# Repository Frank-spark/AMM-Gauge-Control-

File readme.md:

---
## **Project: ESP32 Gauge Control with H2 Integration**

### **Overview**
This project controls an **analog gauge** and **H2 power supply** using an **ESP32-WROOM-32D**. The gauge reflects the **fill level of a tank** based on readings from a **resistance-based float sensor (240Ω - 30Ω)**. The system implements a **soft-start feature** for H2 power supplies to prevent inrush current, and includes a **web configuration interface** for easy parameter adjustment.

### **Features**
✔ Reads **float sensor resistance** and converts it to gauge display using **PWM control**  
✔ **Smooths the gauge movement** to prevent needle shaking  
✔ **Blinks a backlight** when the fill level is low  
✔ **Soft-start control** (0-5V ramping) for H2 power supplies  
✔ **H2 signal detection** from existing H2 board  
✔ Uses **noise-filtered ADC readings** for reliable measurements  
✔ **Web-based configuration interface** for parameter adjustment  
✔ **WiFi connectivity** with fallback AP mode for setup  
✔ **Watchdog signal generation** (10ms interval)  
✔ **12V to 3.3V Buck Converter** power for ESP32  
✔ **12V to 5V Buck Converter** power for 5V components  

---

## **1. Hardware Setup**
### ** Components Needed**
- **ESP32-WROOM-32D**
- **Float Sensor (240Ω - 30Ω)**
- **10kΩ Pull-up Resistor** (for voltage divider)
- **Gauge (0-100% Analog Display)**
- **IRLB8721 MOSFET** (for PWM gauge control)
- **Level Shifter** (for 12V H2 signal input)
- **0-5V DAC/PWM Filter** (for power supply control)
- **330Ω Resistor + LED** (for backlight warning)
- **4-pin I2C Connector** (for future expansion)
- **2x 4.7kΩ Pull-up Resistors** (for I2C)
- **Watchdog Circuit** (connected to Pin 33)

### ** Wiring Guide**
#### **1️ Power Supply**
| Component | Connection |
|-----------|------------|
| ESP32 VIN | **12V from H2 board gauge light** |
| ESP32 GND | **Common Ground** |
 12V to 5V Buck Converters:

#### **2️ Float Sensor (Resistance Measurement)**
| Pin | Connection |
|-----|------------|
| **ESP32 GPIO 34** | **Voltage divider output** |
| **3.3V** | **10kΩ pull-up resistor** → Float Sensor |
| **GND** | **Float Sensor Ground** |

#### **3️ Gauge Control (PWM Output)**
| Pin | Connection |
|-----|------------|
| **ESP32 GPIO 25** | **MOSFET Gate (IRLB8721)** |
| **Gauge (-)** | **MOSFET Drain** |
| **GND** | **MOSFET Source** |

#### **4️ Power Supply Control**
| Pin | Connection |
|-----|------------|
| **ESP32 GPIO 27** | **PWM Filter** → Power Supply Control |
| **Power Supply CC** | **0-5V Control Input** |

#### **5️ H2 Signal Input**
| Pin | Connection |
|-----|------------|
| **ESP32 GPIO 35** | **Level Shifter Output 10k and 39k VD** |
| **Level Shifter Input** | **H2 Board Coil Signal (12V)** |

#### **6️ Backlight Warning**
| Pin | Connection |
|-----|------------|
| **ESP32 GPIO 26** | **LED via 330Ω Resistor** |
| **GND** | **LED Cathode (-)** |

#### **7️ I2C Expansion Port**
| Pin | Connection |
|-----|------------|
| **1** | **3.3V** |
| **2** | **GPIO 21 (SDA) with 4.7kΩ pull-up** |
| **3** | **GPIO 22 (SCL) with 4.7kΩ pull-up** |
| **4** | **GND** |

#### **8️ Watchdog Signal Output**
| Pin | Connection |
|-----|------------|
| **ESP32 GPIO 33** | **Watchdog Circuit Input** |

---

## **Power Supply Selection**

This project requires efficient **DC-DC buck converters** to step down **12V** to the required operating voltages (**5V** and **3.3V**). Below are the recommended surface-mount buck converters:

### **12V to 5V Buck Converters**
1. **Texas Instruments LM2675**  
   - Step-down voltage regulator with **1A** output.  
   - High efficiency, low component count.  
   - Ideal for powering microcontrollers and peripherals.  
   - [Datasheet](https://www.ti.com/lit/ds/symlink/lm2675.pdf)  

2. **Murata Power Solutions OKI-78SR-5/1.5-W36H-C**  
   - Drop-in replacement for traditional **78xx linear regulators**.  
   - Delivers **5V at up to 1.5A** with minimal heat dissipation.  
   - [Datasheet](https://power.murata.com/pub/data/power/oki-78sr.pdf)  

### **12V to 3.3V Buck Converters**
1. **Texas Instruments TPS54331**  
   - Integrated **3A** step-down regulator with **28V input capability**.  
   - Optimized for high efficiency in embedded systems.  
   - [Datasheet](https://www.ti.com/lit/ds/symlink/tps54331.pdf)  

2. **Analog Devices LTC3621**  
   - **1A synchronous buck converter** with **17V input capability**.  
   - Compact and energy-efficient for low-power applications.  
   - [Datasheet](https://www.analog.com/media/en/technical-documentation/data-sheets/LTC3621.pdf)  

### **Selection Considerations**
- **Current Requirements**: Choose a regulator based on the total current draw of your circuits.  
- **Efficiency**: Higher efficiency reduces heat and improves system stability.  
- **Footprint**: Ensure the selected components fit within the PCB layout.  
- **Availability**: Check supplier stock (e.g., [Digi-Key](https://www.digikey.com/) or [Mouser](https://www.mouser.com/)) before finalizing.  

## **2. Code Explanation**
### **⚙ Main Functionalities**
#### **1️ Setup Function**
- Initializes **PWM control for gauge and power supply**
- Sets up **GPIOs for backlight and H2 signal input**
- Starts **watchdog signal generation**
- Initializes **WiFi and web configuration server**

#### **2️ `loop()` Function**
- Monitors **H2 signal** for power control
- Reads **float sensor resistance**
- Controls **gauge display**
- Manages **power supply ramping**
- Handles **low-level warnings**
- Updates **watchdog signal**
- Processes **DNS requests** (in AP mode)

#### **3️ Power Supply Control**
```cpp
void startPEM() {
    // Ramps power supply control from 0V to max value
    for (current_ramp_value = 0; current_ramp_value <= pemMaxValue; current_ramp_value += pemStepSize) {
        ledc_set_duty(LEDC_LOW_SPEED_MODE, PS_PWM_CHANNEL, current_ramp_value);
        ledc_update_duty(LEDC_LOW_SPEED_MODE, PS_PWM_CHANNEL);
        delay(stepDelayMs);
    }
}
```

#### **4️ Read Float Sensor Resistance**
```cpp
float readFloatSensorResistance(int pin) {
    int adcValue = readSmoothADC(pin);
    float voltage = (adcValue / 4095.0) * 3.3;  

    if (voltage <= 0.1) return MAX_RESISTANCE;  

    float resistance = (voltage / (3.3 - voltage)) * knownResistor;
    return resistance;
}
```
- Uses **Ohm's Law** to convert voltage readings to **resistance (240Ω - 30Ω)**.
- **Failsafe:** If voltage is **too low**, assumes an **empty tank (240Ω).**

#### **5️ Smooth ADC Readings**
```cpp
int readSmoothADC(int pin) {
    int total = 0;
    for (int i = 0; i < numSamples; i++) {
        total += analogRead(pin);
        delayMicroseconds(500);
    }
    return total / numSamples;
}
```
- Averages **multiple ADC samples** to **reduce noise**.

#### **6️ Safety Handling**
- **Flashes backlight** when fill level is low
- **Shuts down power supply** by setting control voltage to 0V if level is critically low

#### **7️ Watchdog Signal Generation**
```cpp
void updateWatchdog() {
    unsigned long currentMillis = millis();
    
    // Only enable watchdog after a safe boot period
    if (!watchdogEnabled && (currentMillis - bootTime > WATCHDOG_ENABLE_DELAY)) {
        watchdogEnabled = true;
        Serial.println("Watchdog activated");
    }
    
    // Simply toggle the watchdog pin at the required interval
    if (watchdogEnabled && (currentMillis - lastWatchdogTime >= WATCHDOG_INTERVAL)) {
        lastWatchdogTime = currentMillis;
        digitalWrite(watch_dog, !digitalRead(watch_dog)); // Toggle
    }
}
```
- Generates a **10ms toggle signal** on Pin 33
- Delayed activation allows for **safe boot sequence**

---

## **3.1 Using the Web Configuration Interface**

### **Interface Layout and Navigation**
The web interface is organized into several sections for easy configuration:

1. **Header Section**: Shows the title "Gauge Control Configuration"
2. **Configuration Panels**: Grouped by function (Resistance, PWM, Timing, PEM, WiFi)
3. **Control Buttons**: Save configuration and reset to defaults
4. **Live Monitor**: Real-time data display from the gauge controller
5. **Status Messages**: Appear at the bottom when actions are performed

### **Step-by-Step Configuration Guide**

#### **Resistance Settings Adjustment**
These settings affect how the float sensor readings are interpreted:

1. **Max Resistance (Empty Tank)**: 
   - Default: 240Ω
   - Increase this value if your tank shows "empty" too early
   - Decrease if empty indication happens too late
   - Typical range: 200-300Ω

2. **Min Resistance (Full Tank)**:
   - Default: 30Ω
   - Increase if your tank shows "full" too soon
   - Decrease if the gauge never reaches full
   - Typical range: 20-50Ω

3. **Known Resistor**:
   - Default: 100Ω
   - This is the physical pull-up resistor value in your circuit
   - Only change if you've used a different resistor than specified

#### **PWM Settings Adjustment**
These settings control the gauge needle position:

1. **Min Duty (Empty)**: 
   - Default: 140
   - Controls gauge position when tank is empty
   - Lower value = gauge reads lower when empty
   - Adjust until gauge shows empty correctly

2. **Max Duty (Full)**:
   - Default: 255
   - Controls gauge position when tank is full
   - Higher value = gauge reads higher when full
   - Adjust until gauge shows full correctly

3. **Blink Threshold**:
   - Default: 10
   - Sets level for backlight blinking
   - Increase to start warning earlier (when tank is less empty)
   - Decrease to delay warning (when tank is more empty)

4. **Low Level Threshold**:
   - Default: 145
   - Below this level, power is cut to protect system
   - Should be higher than Blink Threshold but lower than normal operation

#### **PEM Startup Settings**
These settings control the power supply ramp behavior:

1. **Ramp Max Value**: 
   - Default: 255 (maximum PWM)
   - Controls final voltage sent to power supply (0-5V range)
   - Lower for reduced power output
   - Range: 0-255 (0-5V output)

2. **Ramp Step Size**:
   - Default: 1
   - Controls how quickly the voltage ramps up
   - Higher values = faster ramp (less smooth)
   - Lower values = slower ramp (smoother)
   - Recommended range: 1-5

3. **Step Delay**:
   - Default: 20ms
   - Time between voltage steps
   - Longer delay = slower, gentler startup
   - Shorter delay = faster startup
   - Total ramp time = (Max Value ÷ Step Size) × Step Delay

#### **WiFi Settings**
Configure network connectivity:

1. **WiFi SSID**: 
   - Enter your home/office network name
   - Leave blank to remain in AP mode

2. **WiFi Password**:
   - Enter password for your network
   - Will be securely stored in ESP32 memory

### **Using the Live Monitor**
The live monitor shows real-time system status:

- **Resistance**: Current reading from the float sensor (in ohms)
- **Target Duty**: Raw PWM value calculated from resistance
- **Smoothed Duty**: Actual PWM value sent to gauge (after smoothing)
- **PEM Status**: Shows if the power supply is running (green) or stopped (red)

### **Common Adjustments**

1. **Calibrating the Gauge**:
   - With tank empty: Adjust Min Duty until gauge reads empty
   - With tank full: Adjust Max Duty until gauge reads full
   - Fine-tune Min/Max Resistance if needed

2. **Adjusting Response Time**:
   - For faster gauge response: Decrease NORMAL_SMOOTHING in code
   - For smoother movement: Increase NORMAL_SMOOTHING in code
   - Default smoothing values provide good balance

3. **Customizing Power Ramp**:
   - For slower, gentler startup: Increase Step Delay and/or decrease Step Size
   - For faster startup: Decrease Step Delay and/or increase Step Size
   - For lower maximum power: Reduce Max Value

### **Saving and Resetting**

- **Save Configuration**: Click to store all settings in non-volatile memory
- **Reset to Defaults**: Reverts all settings to factory defaults
- Settings persist across power cycles once saved

### **Troubleshooting the Interface**

- **Changes not taking effect**: Ensure you clicked "Save Configuration"
- **Interface not loading**: Check WiFi connection or AP mode
- **Values resetting**: Possible memory corruption; try resetting to defaults
- **Gauge not responding to changes**: Check physical connections

## **3.2 Connecting to the Access Point**

### **Access Point Mode**
When the ESP32 can't connect to a configured WiFi network or no network is configured, it automatically starts in Access Point (AP) mode:

1. **AP Name**: `GaugeControl`
2. **AP Password**: `gaugeconfig`
3. **AP IP Address**: `192.168.4.1`

### **Connection Process**
1. **Power on the ESP32** controller
2. **Wait for initialization** (approximately 5 seconds)
3. **On your phone or computer**:
   - Open WiFi settings
   - Look for the `GaugeControl` network
   - Connect using password `gaugeconfig`
4. **Open a web browser** and navigate to:
   - `http://192.168.4.1`
   - The configuration interface should load automatically

### **Captive Portal**
The system uses a captive portal feature that will:
- Redirect all web requests to the configuration page
- Work similarly to hotel WiFi login pages
- On some devices, a login prompt may appear automatically

### **Station Mode (After Configuration)**
After configuring WiFi credentials and connecting to your network:
1. The ESP32 will connect to your WiFi network
2. The IP address is assigned by your router (DHCP)
3. Check your router's connected devices list to find the assigned IP
4. The serial monitor also displays the assigned IP address at startup

### **Switching Back to AP Mode**
If you need to reconfigure WiFi settings:
1. Power cycle the device 3 times in quick succession OR
2. If previously configured WiFi is unavailable, AP mode starts automatically

### **Troubleshooting Connection Issues**
- **AP not appearing**: Wait 30 seconds after power-on, then try again
- **Can't connect to AP**: Ensure you're using password `gaugeconfig`
- **Can't access 192.168.4.1**: Try disabling mobile data on your phone
- **Connection drops**: Stay within 15 feet (5 meters) of the ESP32

## **4. Expected Behavior**
| **Event** | **Action** | **Response** |
|-----------|------------|--------------|
| **H2 Signal ON** | 12V on GPIO 35 | Start power supply ramp (configurable) |
| **H2 Signal OFF** | 0V on GPIO 35 | Immediate power supply shutdown |
| **Low Tank Level** | PWM < configurable threshold | Backlight starts blinking |
| **Normal Operation** | PWM > threshold | Normal gauge display |
| **Watchdog** | Continuous | 10ms toggle signal on Pin 33 |
| **Power on** | Boot sequence | AP mode if no WiFi configured |

---

## **5. Installation & Usage**
### ** Uploading Code**
1. Open **Arduino IDE**.
2. Install **ESP32 Board Support** via **Boards Manager**.
3. Install required libraries:
   - **ESPAsyncWebServer**
   - **AsyncTCP**
   - **ArduinoJson**
4. Connect **ESP32-WROOM-32D** to USB.
5. Upload `gaugecontrol.ino` and `webui.h`.

### **🔧 Adjusting Settings**
All settings can be adjusted via the web interface. Default values are:
```cpp
#define DEFAULT_MAX_RESISTANCE 240
#define DEFAULT_MIN_RESISTANCE 30
#define DEFAULT_KNOWN_RESISTOR 100
#define DEFAULT_MIN_DUTY 140
#define DEFAULT_MAX_DUTY 255
#define DEFAULT_BLINK_THRESHOLD 10
#define DEFAULT_LOW_LEVEL_THRESHOLD 145
#define DEFAULT_BLINK_INTERVAL 250
#define DEFAULT_NUM_SAMPLES 10
#define DEFAULT_STEP_DELAY_MS 20
#define DEFAULT_PEM_MAX_VALUE 255
#define DEFAULT_PEM_STEP_SIZE 1
```

---

## **6. Troubleshooting**
| **Issue** | **Possible Fix** |
|-----------|------------------|
| **Power supply not ramping** | Check PWM filter circuit and 0-5V output |
| **H2 signal not detected** | Verify level shifter operation and 12V input |
| **Gauge not moving** | Check MOSFET and PWM output |
| **Backlight issues** | Verify LED connections and GPIO 26 |
| **Repeated resets** | Check watchdog circuit and delay settings |
| **Can't access web interface** | Verify WiFi connection or AP mode |

---

## **7. Future Improvements**
🔹 Add **feedback monitoring** from power supply  
🔹 Implement **communication with H2 board**  
🔹 Add **diagnostic LED indicators**  
🔹 Add **I2C sensors or displays**  
🔹 Implement **I2C communication with external devices**  
🔹 Add **OTA firmware updates**  
🔹 Implement **data logging** to monitor system performance  

---

### **Final Notes**
- **This firmware controls an analog gauge, blinks a backlight for warnings, and manages a power supply ramp.**  
- **It provides a web interface for configuration and allows for WiFi connectivity.**
- **The watchdog implementation ensures reliability with external monitoring circuits.**
- **Ensure correct wiring for all circuits to prevent damage.**

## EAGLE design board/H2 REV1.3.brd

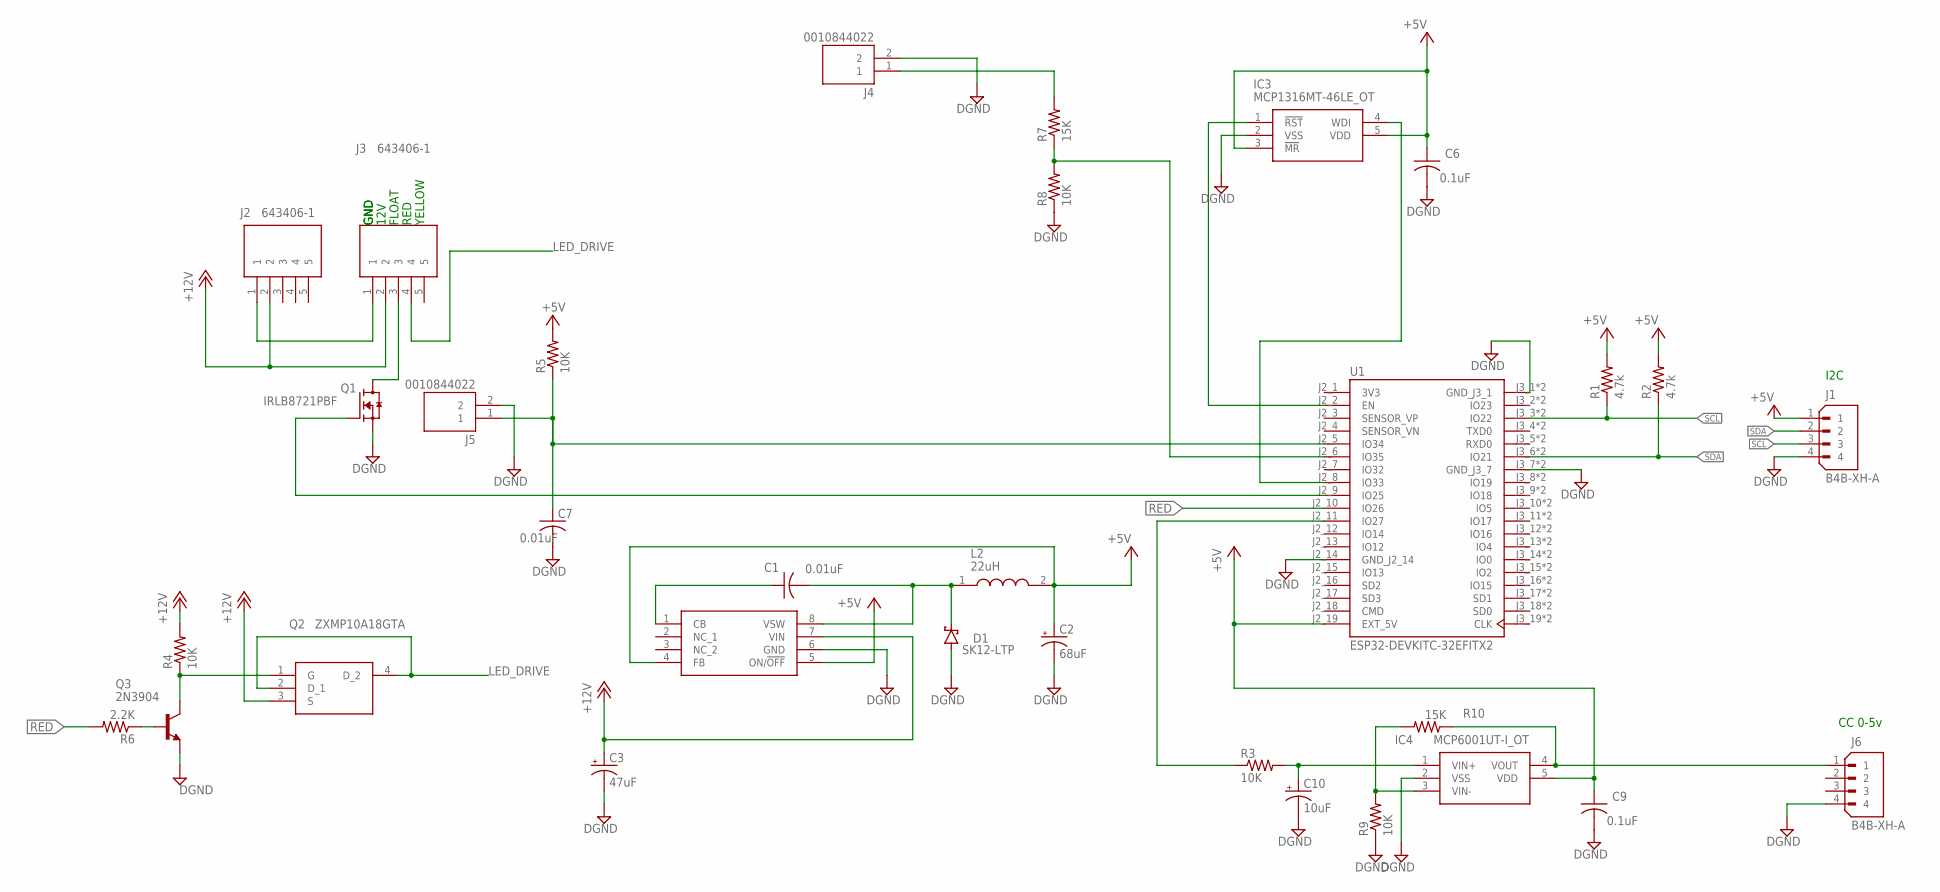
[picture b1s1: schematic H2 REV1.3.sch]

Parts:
C1, C7: 0.01uF; C0805
C2: 68uF; CT3528
C3: 47uF; CT7343
C6, C9: 0.1uF; C0805
C10: 10uF; CT7343
D1: SK12-LTP; SMB
IC2: LM2675M-5.0; SOIC127P600X175-8N
IC3: MCP1316MT-46LE_OT; SOT95P280X145-5N
IC4: MCP6001UT-I_OT; SOT95P280X145-5N
J1, J6: B4B-XH-A; JST_B4B-XH-A
J2, J3: 643406-1; 6434061
J4, J5: 0010844022; MOLEX_0010844022
L2: 22uH; 7447714220
Q1: IRLB8721PBF; TO254P1067X483X2057-3
Q2: ZXMP10A18GTA; SOT230P700X180-4N
Q3: 2N3904; SOT23-EBC
R1, R2: 4.7k; R0805
R3, R5, R8, R9: 10K; R0805
R4: 10K; M0805
R6: 2.2K; M0805
R7, R10: 15K; R0805
U1: ESP32-DEVKITC-32EFITX2; MODULE_ESP32-DEVKITC-32E

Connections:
3V3: U1.J2_1 (3V3)
+5V: C2.+, C6.1, C9.1, IC2.4 (FB), IC2.5 (ON/!OFF), IC3.3 (!MR), IC3.5 (VDD), IC4.5 (VDD), J1.1, L2.2, R1.2, R2.2, R5.2, U1.J2_19 (EXT_5V)
+12V: C3.+, IC2.7 (VIN), J2.2, J3.2, Q2.3 (S), R4.2
DGND: C2.-, C3.-, C6.2, C7.2, C9.2, C10.-, D1.A, IC2.6 (GND), IC3.2 (VSS), IC4.2 (VSS), J1.4, J4.2, J5.2, J6.4, Q1.3 (S), Q3.E, R8.1, R9.1, U1.J2_14 (GND_J2_14), U1.J3_1 (GND_J3_1), U1.J3_7 (GND_J3_7), U1.P$1 (GND_J3_1), U1.P$7 (GND_J3_7)
LED_DRIVE: J3.4, Q2.2 (D_1), Q2.4 (D_2)
unnamed: IC4.4 (VOUT), J6.1, R10.1
unnamed: Q1.1 (G), U1.J2_9 (IO25)
unnamed: J3.3, Q1.2 (D)
unnamed: C10.+, IC4.1 (VIN+), R3.2
unnamed: J4.1, R7.2
unnamed: C1.1, IC2.1 (CB)
unnamed: J2.1, J3.1
unnamed: C1.2, D1.C, IC2.8 (VSW), L2.1
unnamed: R7.1, R8.2, U1.J2_6 (IO35)
unnamed: IC3.1 (!RST), U1.J2_2 (EN)
unnamed: R3.1, U1.J2_11 (IO27)
unnamed: Q3.B, R6.1
unnamed: Q2.1 (G), Q3.C, R4.1
unnamed: C7.1, J5.1, R5.1, U1.J2_5 (IO34)
unnamed: IC3.4 (WDI), U1.J2_8 (IO33)
unnamed: IC4.3 (VIN-), R9.2, R10.2
RED: R6.2, U1.J2_10 (IO26)
SCL: J1.3, R1.1, U1.J3_3 (IO22), U1.P$3 (IO22)
SDA: J1.2, R2.1, U1.J3_6 (IO21), U1.P$6 (IO21)

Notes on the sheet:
I2C
CC 0-5v
GND
12V
FLOAT
RED
YELLOW

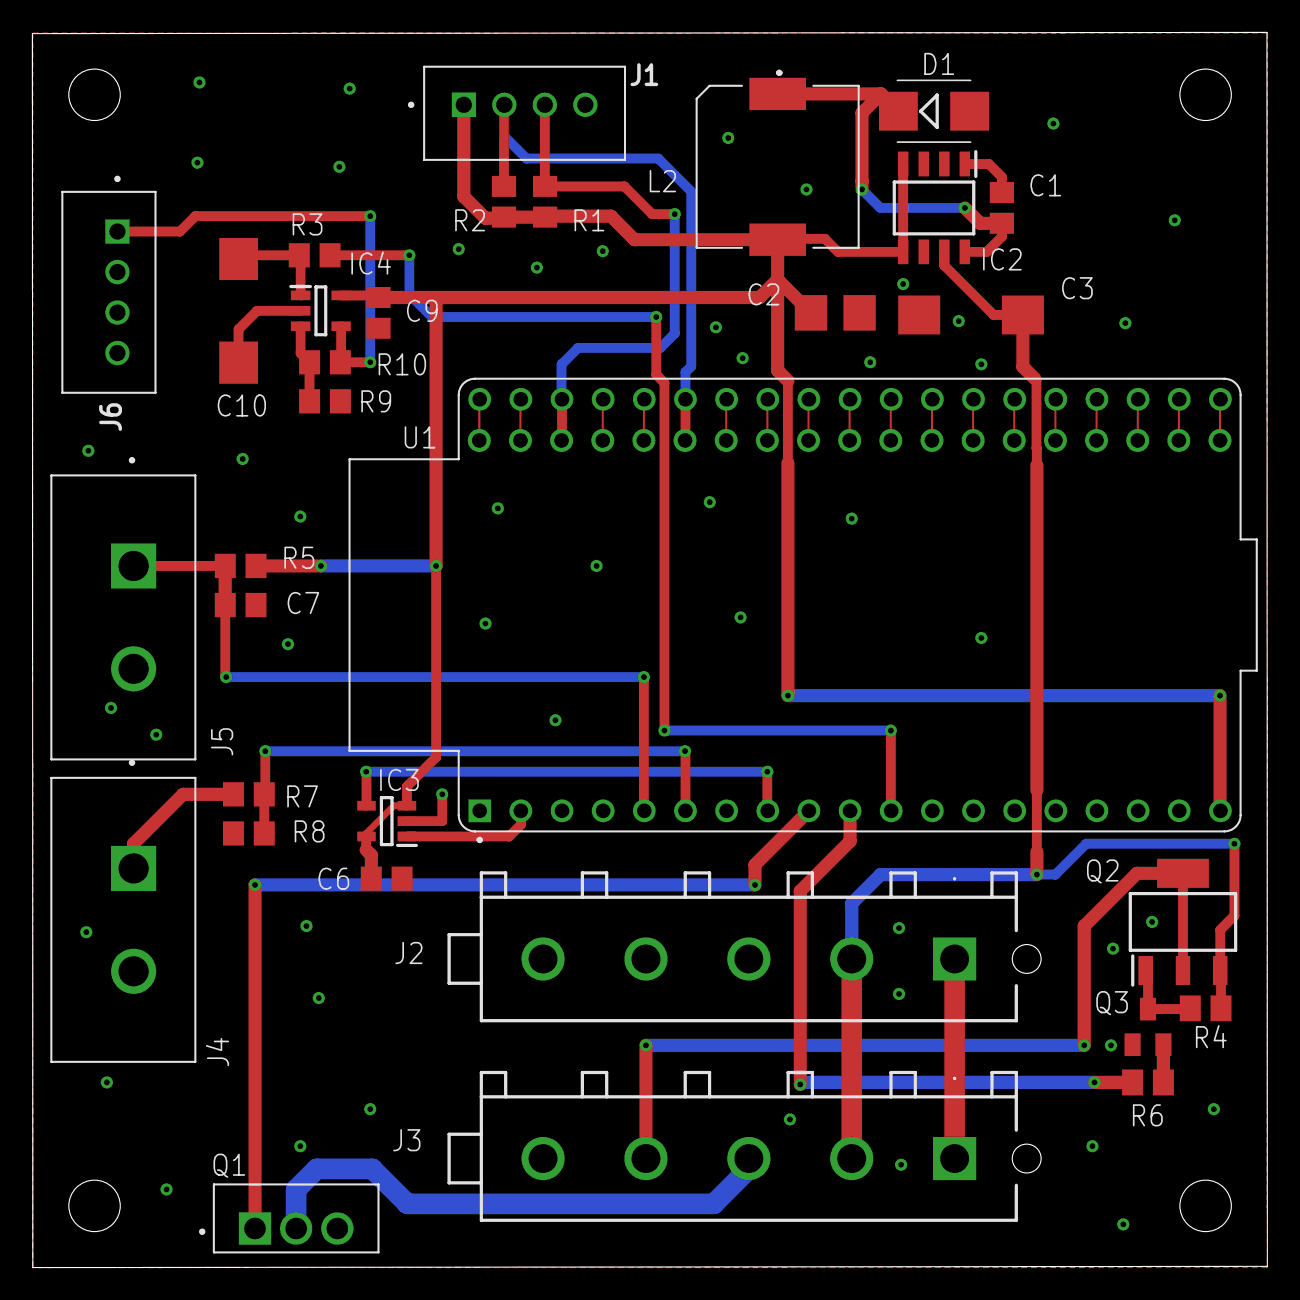
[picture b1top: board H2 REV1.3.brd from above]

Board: 2 copper layers, 76.2 x 76.2 mm, 32 parts (0 on the bottom side), 23 nets.

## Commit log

2025-02-27 Rename pcb.txt to pcb.md
2025-03-10 removed the 110 from the control logic
2025-03-10 I2c added
2025-03-13 Update readme.md
    12v power stepdown selection
2025-03-26 submit board design
2025-04-10 added ui for testing
